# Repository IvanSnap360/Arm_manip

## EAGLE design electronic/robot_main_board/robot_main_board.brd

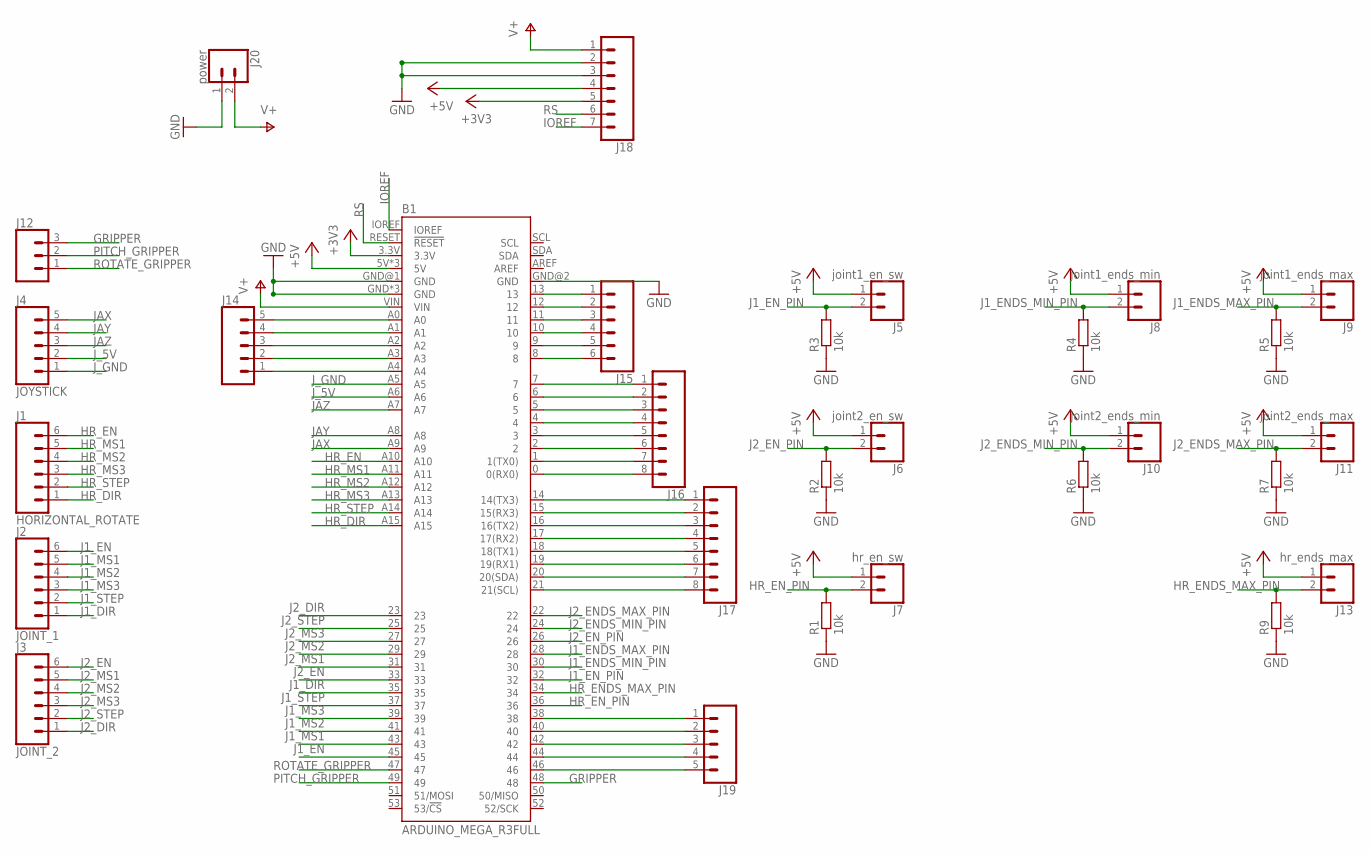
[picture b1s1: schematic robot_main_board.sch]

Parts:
B1: ARDUINO_MEGA_R3FULL; ARDUINO_MEGA_NO_SILK
J1: HORIZONTAL_ROTATE; MOLEX-1X6
J2: JOINT_1; MOLEX-1X6
J3: JOINT_2; MOLEX-1X6
J4: JOYSTICK; 1X05
J5: joint1_en_sw; MOLEX-1X2
J6: joint2_en_sw; MOLEX-1X2
J7: hr_en_sw; MOLEX-1X2
J8: joint1_ends_min; MOLEX-1X2
J9: joint1_ends_max; MOLEX-1X2
J10: joint2_ends_min; MOLEX-1X2
J11: joint2_ends_max; MOLEX-1X2
J12: CONN_03POLAR; MOLEX-1X3
J13: hr_ends_max; MOLEX-1X2
J14, J19: CONN_05; 1X05
J15: CONN_06SILK_FEMALE_PTH; 1X06
J16, J17: CONN_08"; 1X08
J18: CONN_07; 1X07
J20: power; MOLEX-1X2
R1, R2, R3, R4, R5, R6, R7, R9: 10k; 0204/7

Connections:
+3V3: B1.3.3V, J18.5
+5V: B1.5V, B1.5V@1 (5V), B1.5V@2 (5V), J5.1, J6.1, J7.1, J8.1, J9.1, J10.1, J11.1, J13.1, J18.4
GND: B1.GND, B1.GND@1 (GND), B1.GND@2 (GND), B1.GND@3 (GND), B1.GND@4 (GND), J18.2, J18.3, J20.1, R1.1, R2.1, R3.1, R4.1, R5.1, R6.1, R7.1, R9.1
GRIPPER: B1.48, J12.3
HR_DIR: B1.A15, J1.1
HR_EN: B1.A10, J1.6
HR_ENDS_MAX_PIN: B1.34, J13.2, R9.2
HR_EN_PIN: B1.36, J7.2, R1.2
HR_MS1: B1.A11, J1.5
HR_MS2: B1.A12, J1.4
HR_MS3: B1.A13, J1.3
HR_STEP: B1.A14, J1.2
IOREF: B1.IOREF, J18.7
J1_DIR: B1.35, J2.1
J1_EN: B1.45, J2.6
J1_ENDS_MAX_PIN: B1.28, J9.2, R5.2
J1_ENDS_MIN_PIN: B1.30, J8.2, R4.2
J1_EN_PIN: B1.32, J5.2, R3.2
J1_MS1: B1.43, J2.5
J1_MS2: B1.41, J2.4
J1_MS3: B1.39, J2.3
J1_STEP: B1.37, J2.2
J2_DIR: B1.23, J3.1
J2_EN: B1.33, J3.6
J2_ENDS_MAX_PIN: B1.22, J11.2, R7.2
J2_ENDS_MIN_PIN: B1.24, J10.2, R6.2
J2_EN_PIN: B1.26, J6.2, R2.2
J2_MS1: B1.31, J3.5
J2_MS2: B1.29, J3.4
J2_MS3: B1.27, J3.3
J2_STEP: B1.25, J3.2
JAX: B1.A9, J4.5
JAY: B1.A8, J4.4
JAZ: B1.A7, J4.3
J_5V: B1.A6, J4.2
J_GND: B1.A5, J4.1
unnamed: B1.A4, J14.1
unnamed: B1.A3, J14.2
unnamed: B1.A2, J14.3
unnamed: B1.A1, J14.4
unnamed: B1.A0, J14.5
unnamed: B1.13, J15.1
unnamed: B1.12, J15.2
unnamed: B1.11, J15.3
unnamed: B1.10, J15.4
unnamed: B1.9, J15.5
unnamed: B1.8, J15.6
unnamed: B1.7, J16.1
unnamed: B1.6, J16.2
unnamed: B1.5, J16.3
unnamed: B1.4, J16.4
unnamed: B1.3, J16.5
unnamed: B1.2, J16.6
unnamed: B1.1 (1(TX0)), J16.7
unnamed: B1.0 (0(RX0)), J16.8
unnamed: B1.14 (14(TX3)), J17.1
unnamed: B1.15 (15(RX3)), J17.2
unnamed: B1.16 (16(TX2)), J17.3
unnamed: B1.17 (17(RX2)), J17.4
unnamed: B1.18 (18(TX1)), J17.5
unnamed: B1.19 (19(RX1)), J17.6
unnamed: B1.20 (20(SDA)), J17.7
unnamed: B1.21 (21(SCL)), J17.8
unnamed: B1.38, J19.1
unnamed: B1.40, J19.2
unnamed: B1.42, J19.3
unnamed: B1.44, J19.4
unnamed: B1.46, J19.5
PITCH_GRIPPER: B1.49, J12.2
ROTATE_GRIPPER: B1.47, J12.1
RS: B1.RESET (!RESET), J18.6
V+: B1.VIN, J18.1, J20.2

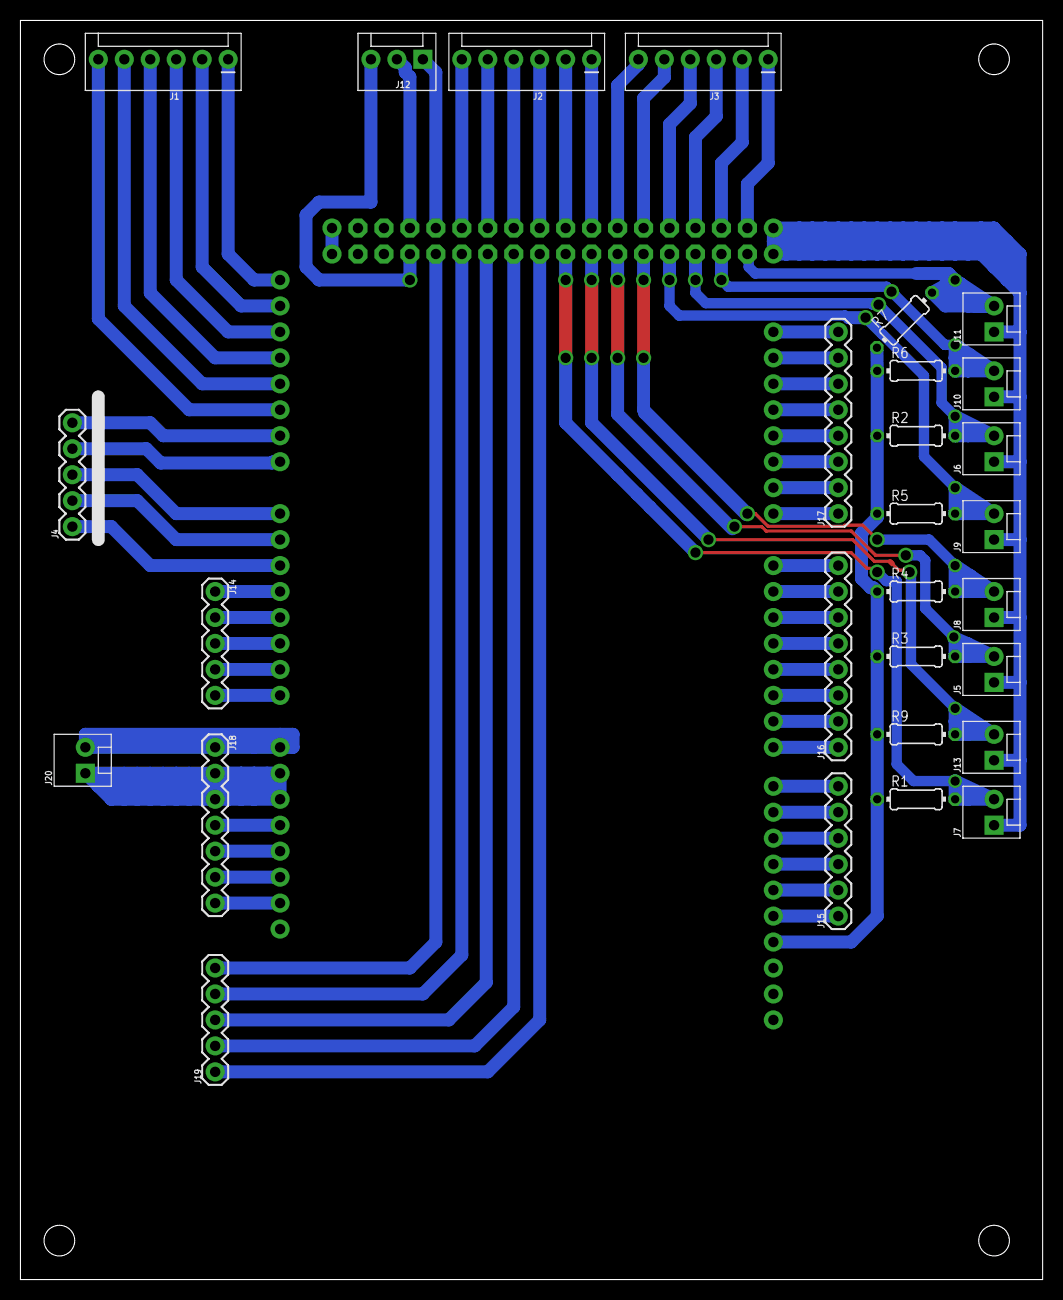
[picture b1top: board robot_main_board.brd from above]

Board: 2 copper layers, 100.0 x 123.2 mm, 29 parts (1 on the bottom side), 72 nets.

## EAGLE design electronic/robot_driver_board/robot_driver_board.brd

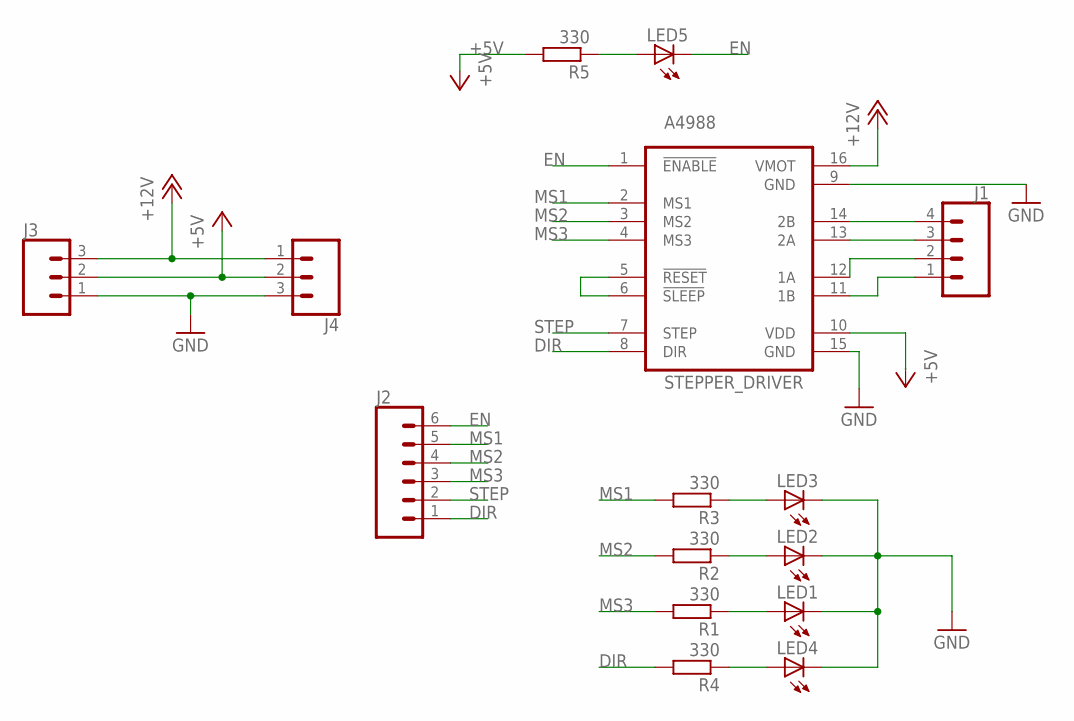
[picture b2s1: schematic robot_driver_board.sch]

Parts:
J1: CONN_04POLAR; MOLEX-1X4
J2: CONN_06POLAR; MOLEX-1X6
J3, J4: CONN_03-SCREW-5MM; SCREWTERMINAL-5MM-3
LED1, LED2, LED3, LED4, LED5: LED3MM
R1: 330; 0207/10
R2, R3, R4, R5: 330; 0204/7
STEPPER_DRIVER: A4988; POLOLULU2128

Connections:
+5V: J3.2, J4.2, R5.2, STEPPER_DRIVER.10 (VDD)
+12V: J3.3, J4.1, STEPPER_DRIVER.16 (VMOT)
DIR: J2.1, R4.2, STEPPER_DRIVER.8 (DIR)
EN: J2.6, LED5.K (C), STEPPER_DRIVER.1 (!ENABLE)
GND: J3.1, J4.3, LED1.K (C), LED2.K (C), LED3.K (C), LED4.K (C), STEPPER_DRIVER.9 (GND), STEPPER_DRIVER.15 (GND)
MS1: J2.5, R3.2, STEPPER_DRIVER.2 (MS1)
MS2: J2.4, R2.2, STEPPER_DRIVER.3 (MS2)
MS3: J2.3, R1.2, STEPPER_DRIVER.4 (MS3)
unnamed: J1.4, STEPPER_DRIVER.14 (2B)
unnamed: J1.3, STEPPER_DRIVER.13 (2A)
unnamed: J1.2, STEPPER_DRIVER.12 (1A)
unnamed: STEPPER_DRIVER.5 (!RESET), STEPPER_DRIVER.6 (!SLEEP)
unnamed: J1.1, STEPPER_DRIVER.11 (1B)
unnamed: LED1.A, R1.1
unnamed: LED2.A, R2.1
unnamed: LED3.A, R3.1
unnamed: LED4.A, R4.1
unnamed: LED5.A, R5.1
STEP: J2.2, STEPPER_DRIVER.7 (STEP)

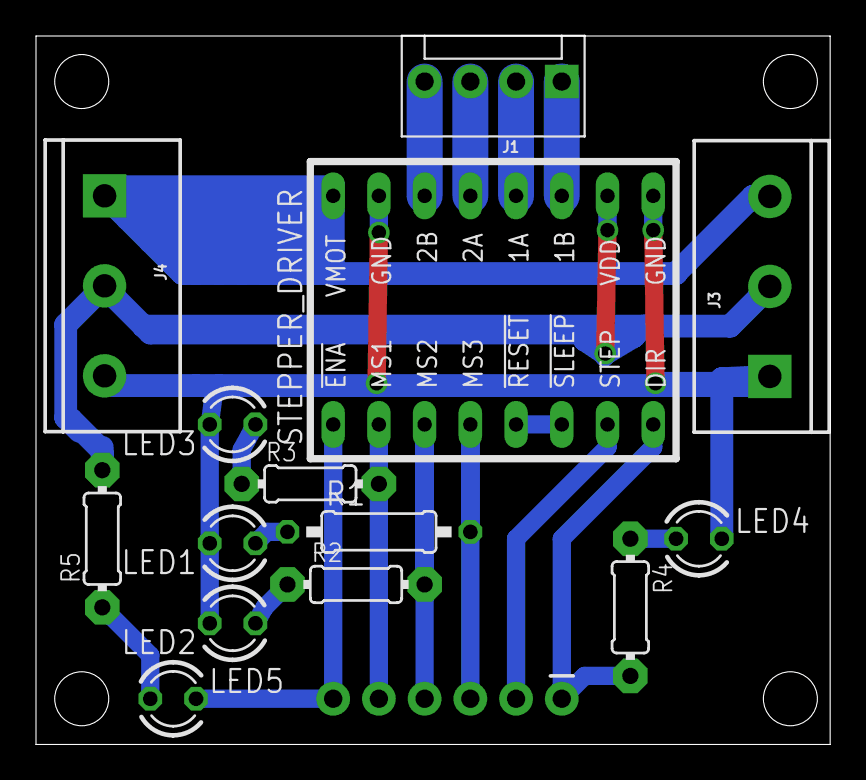
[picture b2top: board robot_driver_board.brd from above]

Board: 2 copper layers, 44.1 x 39.4 mm, 15 parts (1 on the bottom side), 19 nets.

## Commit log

2019-12-26 Add files
2019-12-26 add rotate joint
2019-12-26 upgrade joint2 rotate part
2019-12-29 add joint 3
2019-12-29 Change structure of project
2019-12-30 Add plane of gripper
2020-01-04 add something for electronic part
2020-01-05 change robot_main_board
2020-01-06 add power board

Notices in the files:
parts and their libraries:
SparkFun-Connectors: Licensing: Creative Commons ShareAlike 4.0 International - https://creativecommons.org/licenses/by-sa/4.0
